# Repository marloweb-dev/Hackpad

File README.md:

# Hackpad
Cutom keypad for the stardance hackpad challenge

My hackpad has 5 keys, a rotary encoder, a led status bar and an oled display. It uses QMK firmware.

## PCB
Here is the pcb I made in Kicad:

## CAD design
At first for this case I attempted to learn fusion but due to time constraints I pivoted to tinkercad in order to finish on time. The case itself is made up of a base and a lid. I forgot to export the fancy pcb with all the components so apologies for that.

## BOM
For this project I used:

* 5x Cherry MX Switches
* 5x DSA Keycaps
* 6x 1N4148 DO-35 Diodes
* 6x SK6812 MINI-E LEDs
* 1x 0.91" 128x32 OLED Display
* 1x EC11 Rotary Encoder
* 1x XIAO RP2040
* 1x Case (2 3d printed parts)

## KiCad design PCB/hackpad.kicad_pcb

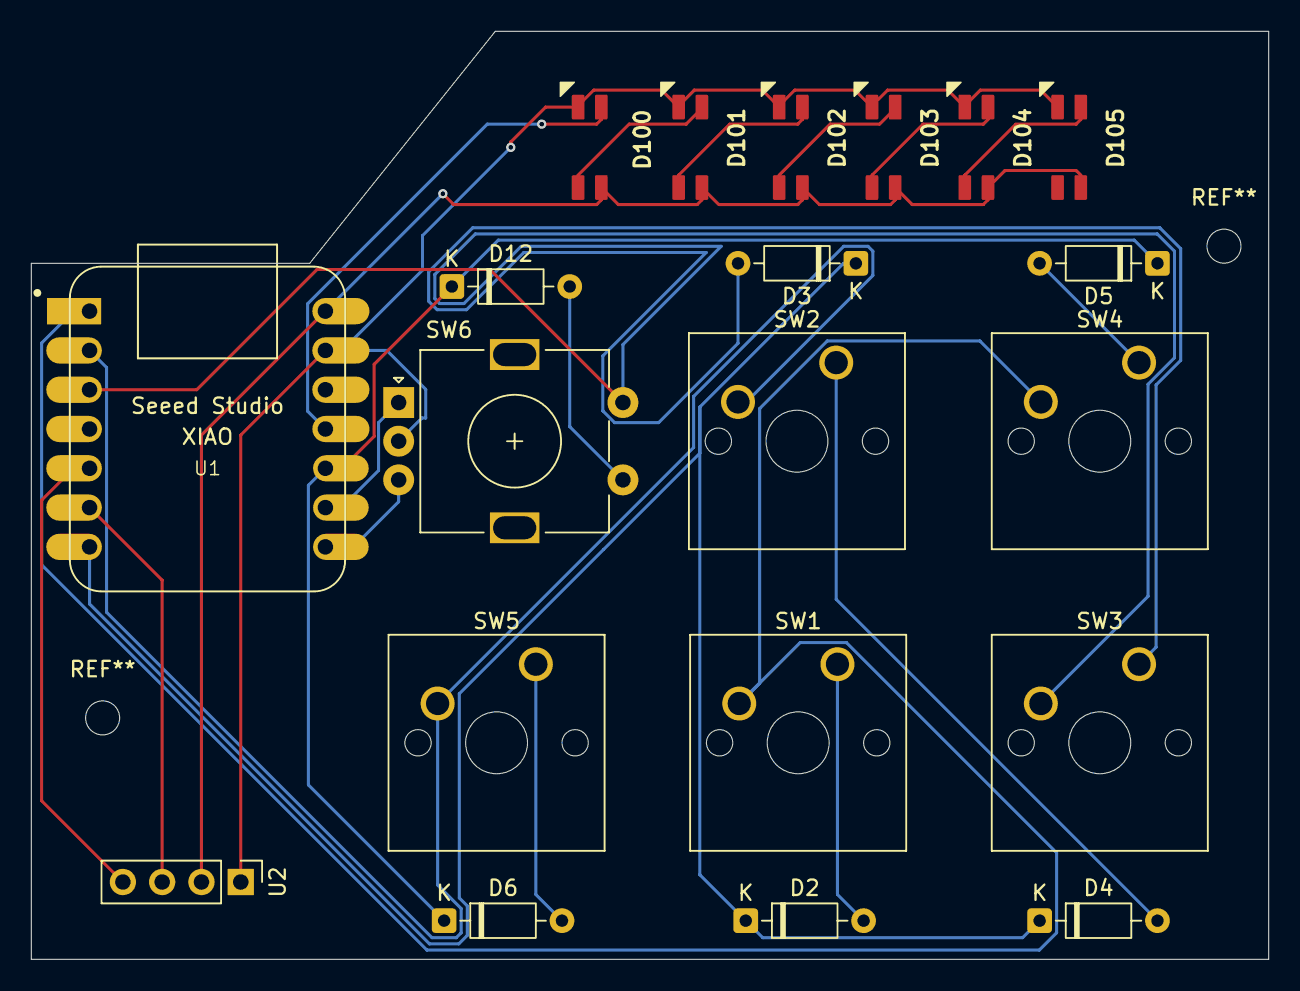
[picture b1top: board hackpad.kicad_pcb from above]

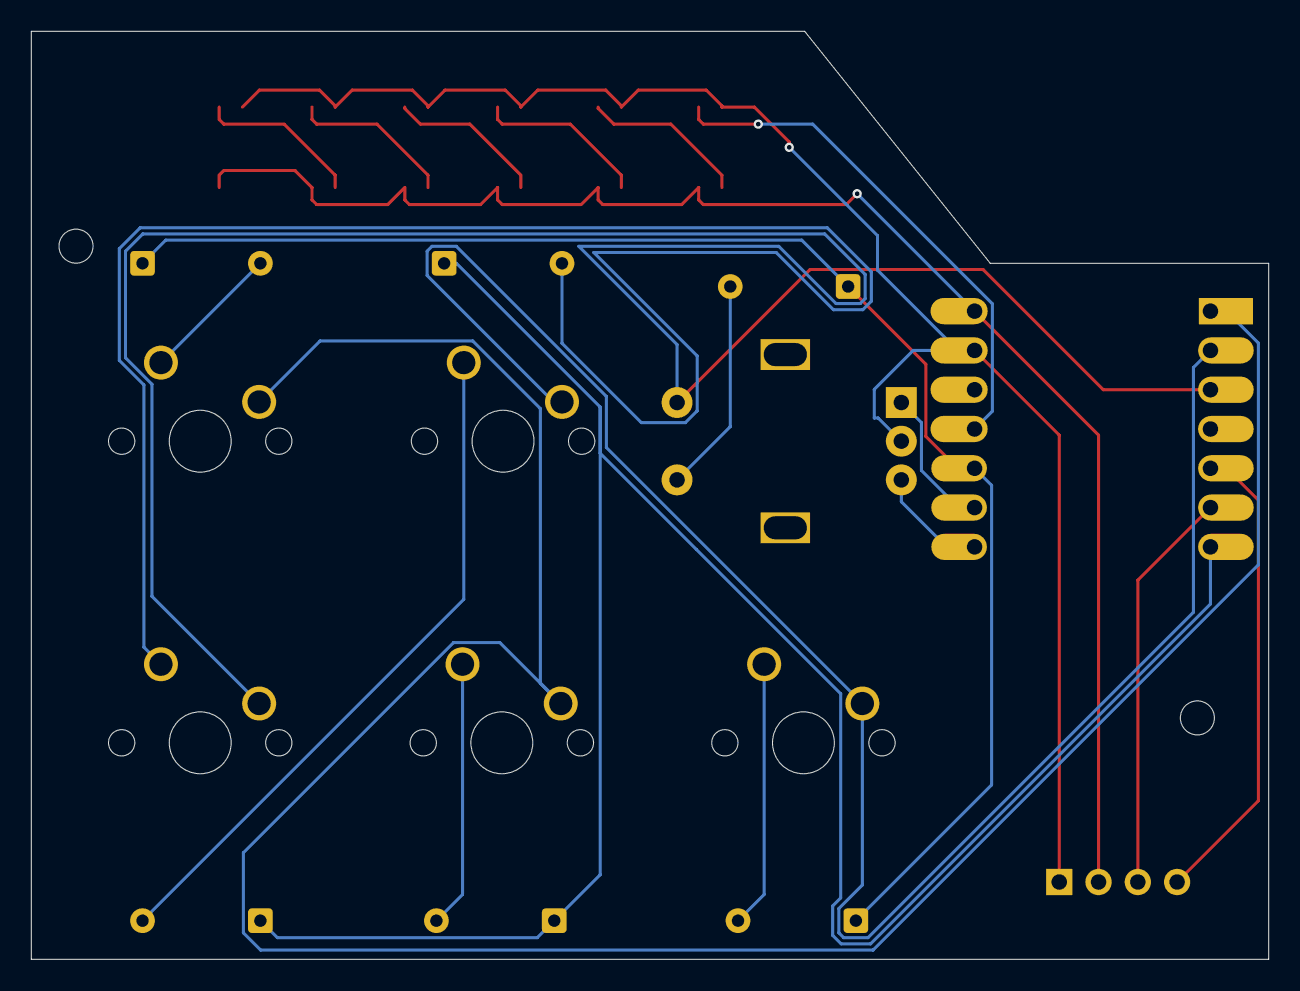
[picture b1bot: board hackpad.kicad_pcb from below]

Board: 2 copper layers, 80.0 x 60.0 mm, 20 parts (6 on the bottom side), 23 nets.

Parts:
D2, D3, D4, D5, D6, D12: D; D_DO-35_SOD27_P7.62mm_Horizontal
D100, D101, D102, D103, D104, D105: SK6812MINI-E_fixed
SW1, SW2, SW3, SW4, SW5: SW_Push; SW_Cherry_MX_1.00u_PCB
SW6: RotaryEncoder_Switch; RotaryEncoder_Alps_EC11E-Switch_Vertical_H20mm
U1: MOUDLE-SEEEDUINO-XIAO; XIAO-Generic-Hybrid-14P-2.54-21X17.8MM
U2: PinHeader_1x04_P2.54mm_Vertical

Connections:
COL1: SW1.2, SW4.2, U1.1 (PA02_A0_D0)
COL2: SW2.2, SW5.2, U1.2 (PA4_A1_D1)
COL3: SW3.2, SW6.S2, U1.3 (PA10_A2_D2)
GND: D100.3 (VSS), D101.3 (VSS), D102.3 (VSS), D103.3 (VSS), D104.3 (VSS), D105.3 (VSS), SW6.C, U1.13 (GND), U2.1 (GND)
LEDS: D100.4 (DIN), U1.11 (PA6_A10_D10_MOSI)
unnamed: D2.2 (A), SW1.1
unnamed: D3.2 (A), SW3.1
unnamed: D4.2 (A), SW2.1
unnamed: D5.2 (A), SW4.1
unnamed: D6.2 (A), SW5.1
unnamed: D100.2 (DOUT), D101.4 (DIN)
unnamed: D101.2 (DOUT), D102.4 (DIN)
unnamed: D102.2 (DOUT), D103.4 (DIN)
unnamed: D103.2 (DOUT), D104.4 (DIN)
unnamed: D104.2 (DOUT), D105.4 (DIN)
REA: SW6.A, U1.9 (PA7_A8_D8_SCK)
REB: SW6.B, U1.8 (PB09_A7_D7_RX)
RES1: D12.2 (A), SW6.S1
ROW1: D2.1 (K), D3.1 (K), D4.1 (K), U1.7 (PB08_A6_D6_TX)
ROW2: D5.1 (K), D6.1 (K), D12.1 (K), U1.10 (PA5_A9_D9_MISO)
SCL: U1.6 (PA9_A5_D5_SCL), U2.3 (SCL)
SDA: U1.5 (PA8_A4_D4_SDA), U2.4 (SDA)
VCC: D100.1 (VDD), D101.1 (VDD), D102.1 (VDD), D103.1 (VDD), D104.1 (VDD), D105.1 (VDD), U1.14 (5V), U2.2 (VCC)

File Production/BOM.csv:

Quantity,Part,Description,Reference Designator(s)
5,Cherry MX Switch,Mechanical keyboard switch,"SW1,SW2,SW3,SW4,SW5"
5,DSA Keycap,Keycap for MX-style switches,
6,1N4148 DO-35,Signal diode (switch matrix),"D2,D3,D4,D5,D6,D12"
6,SK6812MINI-E,Addressable RGB LED,
1,SSD1306 OLED Display,0.91" 128x32 I2C OLED display,U2
1,EC11 Rotary Encoder,Rotary encoder with push switch,SW6
1,Seeed XIAO RP2040,Main microcontroller,U1
2,3D Printed Case Part,Base and lid,
